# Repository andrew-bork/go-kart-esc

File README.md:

# go-kart-esc
 VROOM, 40A/40A 12-50V Dual Channel Brushed ESC

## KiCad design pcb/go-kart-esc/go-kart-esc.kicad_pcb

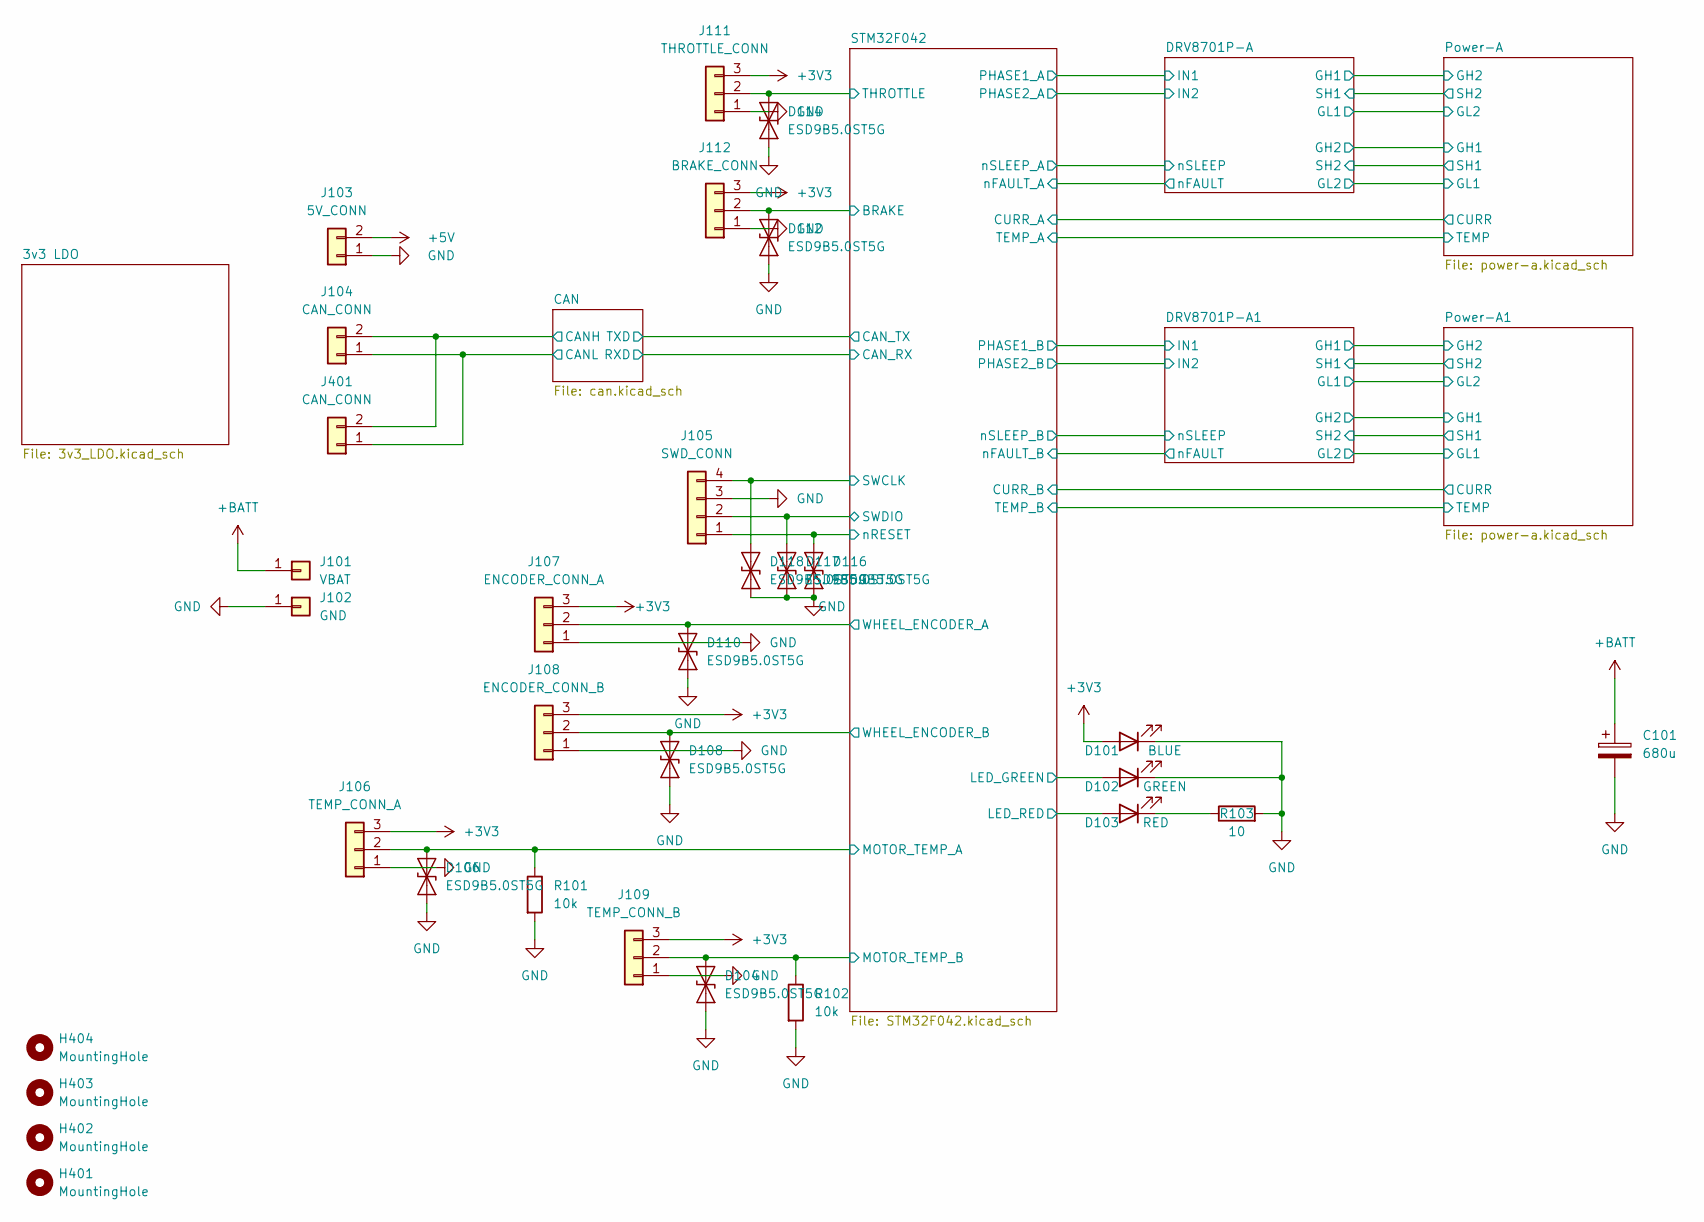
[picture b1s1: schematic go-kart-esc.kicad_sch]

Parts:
C101: 680u; CP_Radial_D16.0mm_P7.50mm
D101: BLUE; LED_0603_1608Metric_Pad1.05x0.95mm_HandSolder
D102: GREEN; LED_0603_1608Metric_Pad1.05x0.95mm_HandSolder
D103: RED; LED_0603_1608Metric_Pad1.05x0.95mm_HandSolder
D104, D106, D108, D110, D112, D114, D116, D117, D118: ESD9B5.0ST5G; D_SOD-923
H401, H402, H403, H404: MountingHole; MountingHole_3.2mm_M3
J101: VBAT; Motor_Solder_Pad
J102: GND; Motor_Solder_Pad
J103: 5V_CONN; JST_XH_S2B-XH-A-1_1x02_P2.50mm_Horizontal
J104, J401: CAN_CONN; JST_XH_S2B-XH-A_1x02_P2.50mm_Horizontal
J105: SWD_CONN; PinHeader_2x02_P2.54mm_Vertical
J106: TEMP_CONN_A; JST_XH_S3B-XH-A_1x03_P2.50mm_Horizontal
J107: ENCODER_CONN_A; JST_XH_S3B-XH-A_1x03_P2.50mm_Horizontal
J108: ENCODER_CONN_B; JST_XH_S3B-XH-A_1x03_P2.50mm_Horizontal
J109: TEMP_CONN_B; JST_XH_S3B-XH-A_1x03_P2.50mm_Horizontal
J111: THROTTLE_CONN; JST_XH_S3B-XH-A_1x03_P2.50mm_Horizontal
J112: BRAKE_CONN; JST_XH_S3B-XH-A_1x03_P2.50mm_Horizontal
R101, R102: 10k; R_0402_1005Metric_Pad0.72x0.64mm_HandSolder
R103: 10; R_0603_1608Metric_Pad0.98x0.95mm_HandSolder

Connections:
+3V3: D101.2 (A), J106.3, J107.3, J108.3, J109.3, J111.3, J112.3; also elsewhere on the board
+5V: J103.2; also elsewhere on the board
+BATT: C101.1, J101.1; also elsewhere on the board
/CAN/CANH: J104.2, J401.2; also elsewhere on the board
/CAN/CANL: J104.1, J401.1; also elsewhere on the board
/STM32F042/BRAKE: D112.2 (A2), J112.2; also elsewhere on the board
/STM32F042/LED_GREEN: D102.2 (A); also elsewhere on the board
/STM32F042/LED_RED: D103.2 (A); also elsewhere on the board
/STM32F042/MOTOR_TEMP_A: D106.2 (A2), J106.2, R101.1; also elsewhere on the board
/STM32F042/MOTOR_TEMP_B: D104.2 (A2), J109.2, R102.1; also elsewhere on the board
/STM32F042/SWCLK: D118.2 (A2), J105.4; also elsewhere on the board
/STM32F042/SWDIO: D117.2 (A2), J105.2; also elsewhere on the board
/STM32F042/THROTTLE: D114.2 (A2), J111.2; also elsewhere on the board
/STM32F042/WHEEL_ENCODER_A: D110.2 (A2), J107.2; also elsewhere on the board
/STM32F042/WHEEL_ENCODER_B: D108.2 (A2), J108.2; also elsewhere on the board
/STM32F042/nRESET: D116.2 (A2), J105.1; also elsewhere on the board
GND: C101.2, D101.1 (K), D102.1 (K), D104.1 (A1), D106.1 (A1), D108.1 (A1), D110.1 (A1), D112.1 (A1), D114.1 (A1), D116.1 (A1), D117.1 (A1), D118.1 (A1), J102.1, J103.1, J105.3, J106.1, J107.1, J108.1, J109.1, J111.1, J112.1, R101.2, R102.2, R103.2; also elsewhere on the board
unnamed: D103.1 (K), R103.1

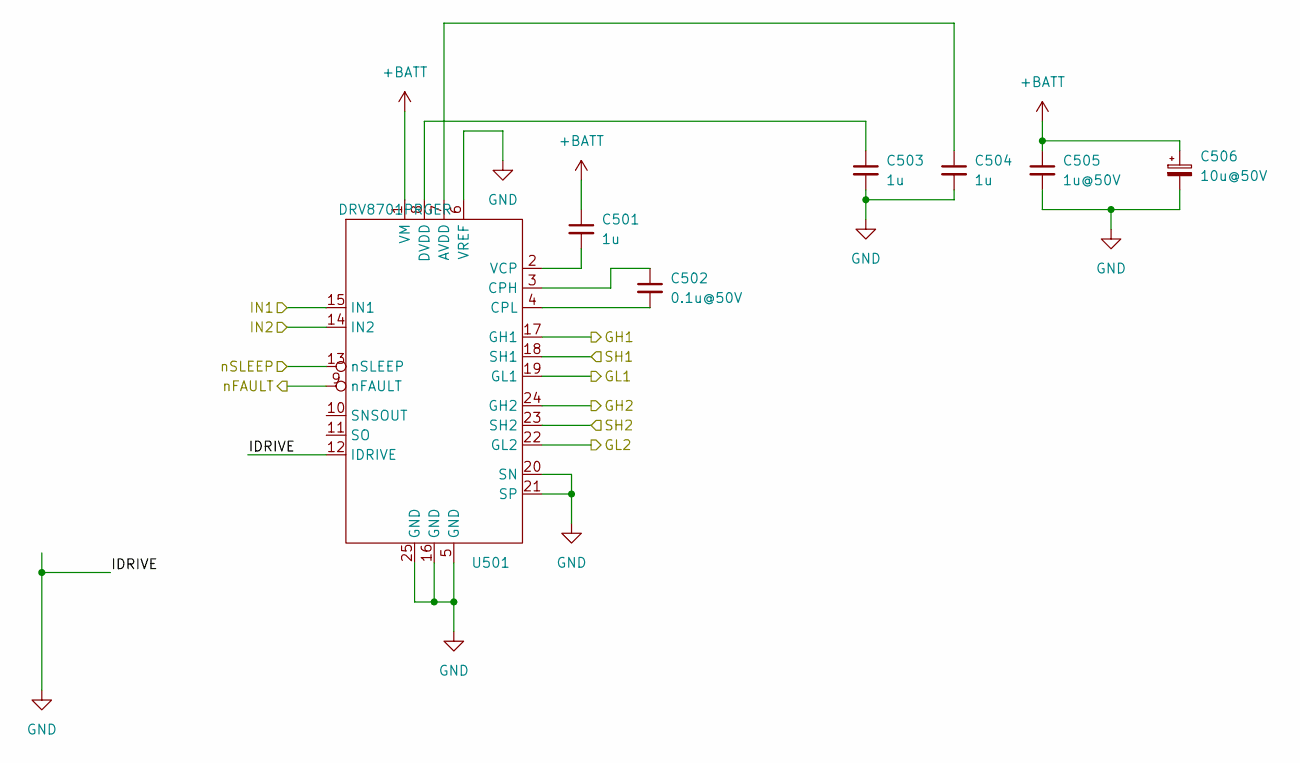
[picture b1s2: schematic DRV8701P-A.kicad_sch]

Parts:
C501, C503, C504: 1u; C_0402_1005Metric_Pad0.74x0.62mm_HandSolder
C502: 0.1u@50V; C_0603_1608Metric_Pad1.08x0.95mm_HandSolder
C505: 1u@50V; C_0402_1005Metric_Pad0.74x0.62mm_HandSolder
C506: 10u@50V; CP_Elec_5x5.8
U501: DRV8701PRGER; Texas_S-PVQFN-N24_EP2.1x2.1mm

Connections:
+BATT: C501.1, C505.1, C506.1, U501.1 (VM); also elsewhere on the board
/DRV8701P-A1/GH1: U501.17 (GH1); also elsewhere on the board
/DRV8701P-A1/GH2: U501.24 (GH2); also elsewhere on the board
/DRV8701P-A1/GL1: U501.19 (GL1); also elsewhere on the board
/DRV8701P-A1/GL2: U501.22 (GL2); also elsewhere on the board
/DRV8701P-A1/IN1: U501.15 (IN1); also elsewhere on the board
/DRV8701P-A1/IN2: U501.14 (IN2); also elsewhere on the board
/DRV8701P-A1/SH1: U501.18 (SH1); also elsewhere on the board
/DRV8701P-A1/SH2: U501.23 (SH2); also elsewhere on the board
/DRV8701P-A1/nFAULT: U501.9 (nFAULT); also elsewhere on the board
/DRV8701P-A1/nSLEEP: U501.13 (nSLEEP); also elsewhere on the board
GND: C503.2, C504.2, C505.2, C506.2, U501.5 (GND), U501.6 (VREF), U501.12 (IDRIVE), U501.16 (GND), U501.20 (SN), U501.21 (SP), U501.25 (GND); also elsewhere on the board
unnamed: C504.1, U501.7 (AVDD)
unnamed: C502.1, U501.3 (CPH)
unnamed: C502.2, U501.4 (CPL)
unnamed: C503.1, U501.8 (DVDD)
unnamed: C501.2, U501.2 (VCP)

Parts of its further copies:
C201, C203, C204: 1u; C_0402_1005Metric_Pad0.74x0.62mm_HandSolder
C202: 0.1u@50V; C_0603_1608Metric_Pad1.08x0.95mm_HandSolder
C205: 1u@50V; C_0402_1005Metric_Pad0.74x0.62mm_HandSolder
C206: 10u@50V; CP_Elec_5x5.8
U201: DRV8701PRGER; Texas_S-PVQFN-N24_EP2.1x2.1mm

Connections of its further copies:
+BATT: C201.1, C205.1, C206.1, U201.1 (VM); also elsewhere on the board
/DRV8701P-A/GH1: U201.17 (GH1); also elsewhere on the board
/DRV8701P-A/GH2: U201.24 (GH2); also elsewhere on the board
/DRV8701P-A/GL1: U201.19 (GL1); also elsewhere on the board
/DRV8701P-A/GL2: U201.22 (GL2); also elsewhere on the board
/DRV8701P-A/IN1: U201.15 (IN1); also elsewhere on the board
/DRV8701P-A/IN2: U201.14 (IN2); also elsewhere on the board
/DRV8701P-A/SH1: U201.18 (SH1); also elsewhere on the board
/DRV8701P-A/SH2: U201.23 (SH2); also elsewhere on the board
/DRV8701P-A/nFAULT: U201.9 (nFAULT); also elsewhere on the board
/DRV8701P-A/nSLEEP: U201.13 (nSLEEP); also elsewhere on the board
GND: C203.2, C204.2, C205.2, C206.2, U201.5 (GND), U201.6 (VREF), U201.12 (IDRIVE), U201.16 (GND), U201.20 (SN), U201.21 (SP), U201.25 (GND); also elsewhere on the board
unnamed: C204.1, U201.7 (AVDD)
unnamed: C202.1, U201.3 (CPH)
unnamed: C202.2, U201.4 (CPL)
unnamed: C203.1, U201.8 (DVDD)
unnamed: C201.2, U201.2 (VCP)

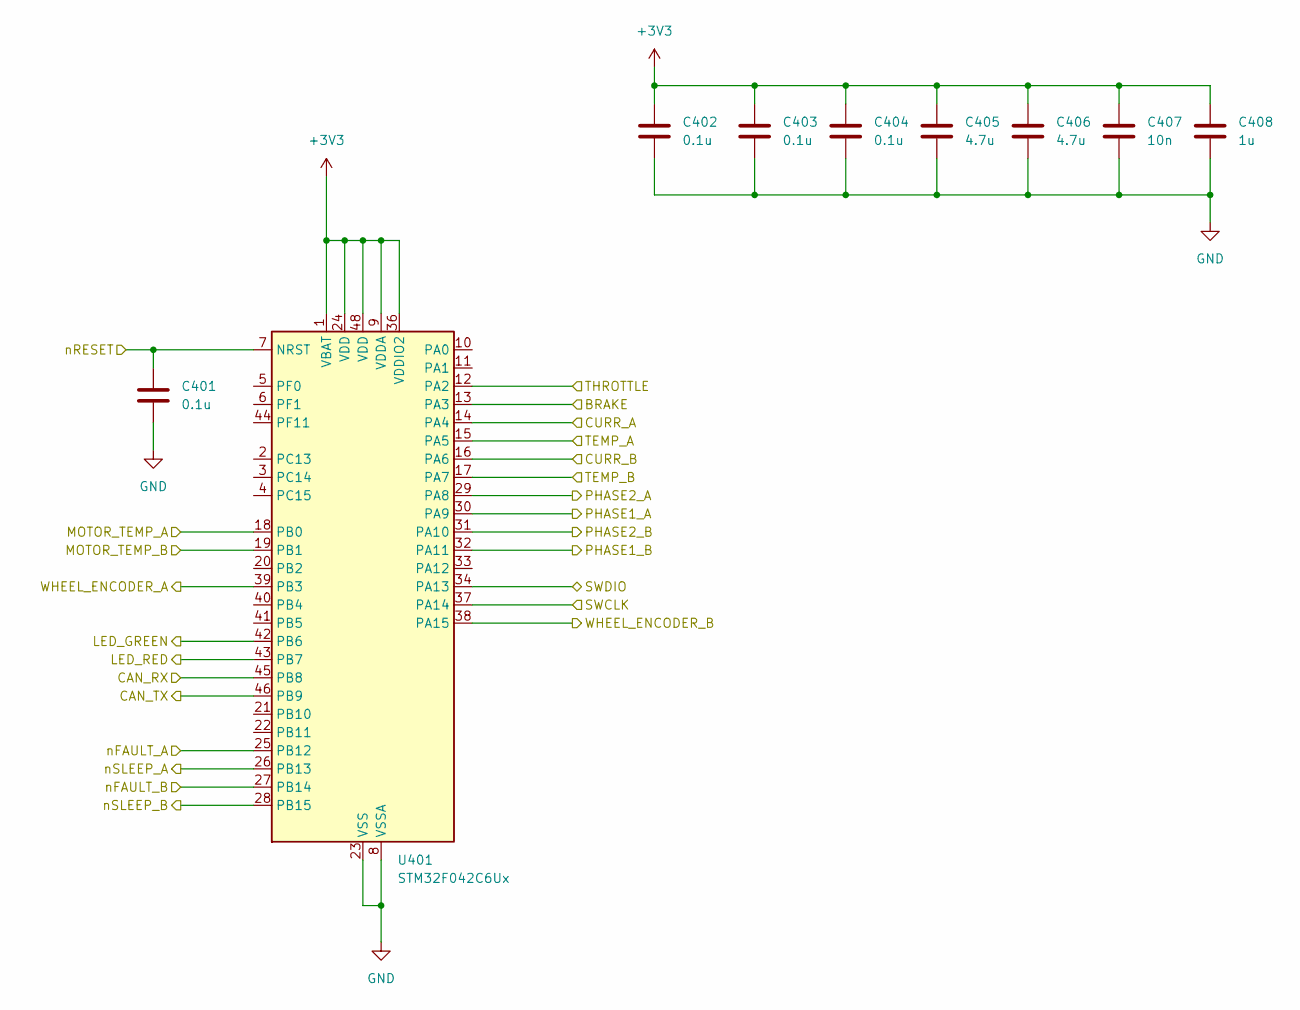
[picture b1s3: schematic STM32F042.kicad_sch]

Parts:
C401, C402, C403, C404: 0.1u; C_0402_1005Metric_Pad0.74x0.62mm_HandSolder
C405, C406: 4.7u; C_0603_1608Metric_Pad1.08x0.95mm_HandSolder
C407: 10n; C_0402_1005Metric_Pad0.74x0.62mm_HandSolder
C408: 1u; C_0402_1005Metric_Pad0.74x0.62mm_HandSolder
U401: STM32F042C6Ux; QFN-48-1EP_7x7mm_P0.5mm_EP5.6x5.6mm

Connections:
+3V3: C402.1, C403.1, C404.1, C405.1, C406.1, C407.1, C408.1, U401.1 (VBAT), U401.9 (VDDA), U401.24 (VDD), U401.36 (VDDIO2), U401.48 (VDD); also elsewhere on the board
/CAN/RXD: U401.45 (PB8); also elsewhere on the board
/CAN/TXD: U401.46 (PB9); also elsewhere on the board
/DRV8701P-A1/IN1: U401.32 (PA11); also elsewhere on the board
/DRV8701P-A1/IN2: U401.31 (PA10); also elsewhere on the board
/DRV8701P-A1/nFAULT: U401.27 (PB14); also elsewhere on the board
/DRV8701P-A1/nSLEEP: U401.28 (PB15); also elsewhere on the board
/DRV8701P-A/IN1: U401.30 (PA9); also elsewhere on the board
/DRV8701P-A/IN2: U401.29 (PA8); also elsewhere on the board
/DRV8701P-A/nFAULT: U401.25 (PB12); also elsewhere on the board
/DRV8701P-A/nSLEEP: U401.26 (PB13); also elsewhere on the board
/Power-A1/CURR: U401.16 (PA6); also elsewhere on the board
/Power-A1/TEMP: U401.17 (PA7); also elsewhere on the board
/Power-A/CURR: U401.14 (PA4); also elsewhere on the board
/Power-A/TEMP: U401.15 (PA5); also elsewhere on the board
/STM32F042/BRAKE: U401.13 (PA3); also elsewhere on the board
/STM32F042/LED_GREEN: U401.42 (PB6); also elsewhere on the board
/STM32F042/LED_RED: U401.43 (PB7); also elsewhere on the board
/STM32F042/MOTOR_TEMP_A: U401.18 (PB0); also elsewhere on the board
/STM32F042/MOTOR_TEMP_B: U401.19 (PB1); also elsewhere on the board
/STM32F042/SWCLK: U401.37 (PA14); also elsewhere on the board
/STM32F042/SWDIO: U401.34 (PA13); also elsewhere on the board
/STM32F042/THROTTLE: U401.12 (PA2); also elsewhere on the board
/STM32F042/WHEEL_ENCODER_A: U401.39 (PB3); also elsewhere on the board
/STM32F042/WHEEL_ENCODER_B: U401.38 (PA15); also elsewhere on the board
/STM32F042/nRESET: C401.1, U401.7 (NRST); also elsewhere on the board
GND: C401.2, C402.2, C403.2, C404.2, C405.2, C406.2, C407.2, C408.2, U401.8 (VSSA), U401.23 (VSS), U401.35 (VSS), U401.47 (VSS), U401.49 (VSS); also elsewhere on the board

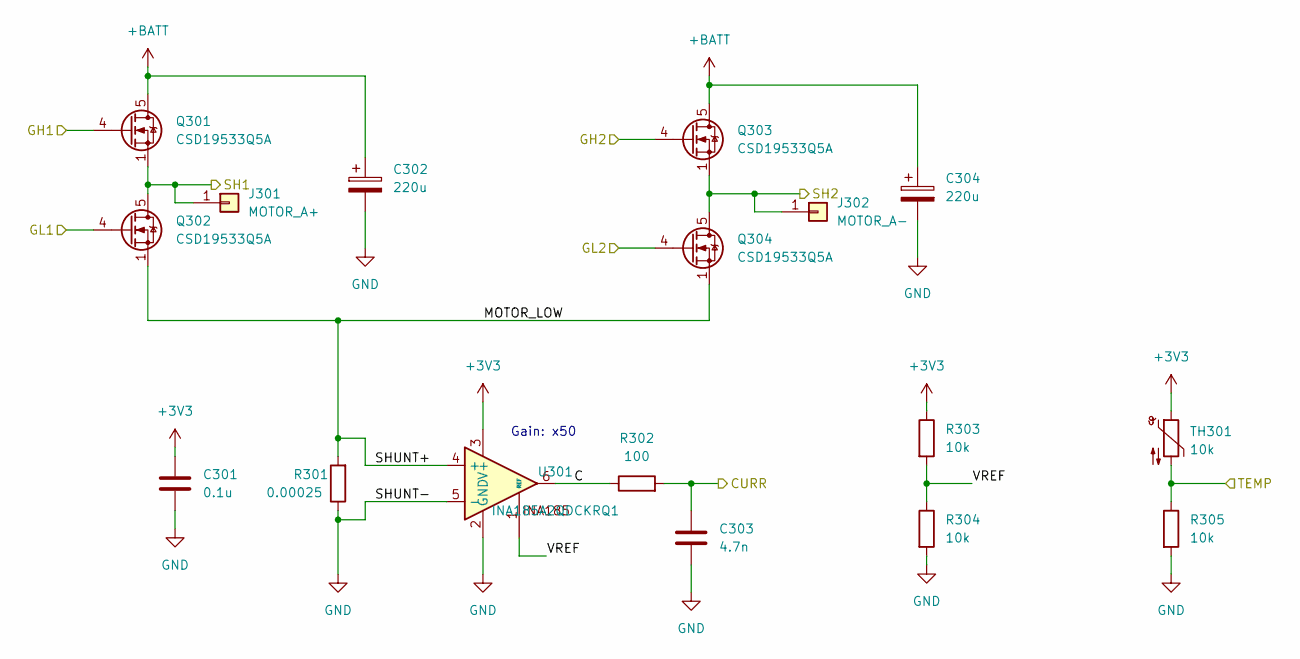
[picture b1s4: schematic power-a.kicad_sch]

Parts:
C301: 0.1u; C_0402_1005Metric_Pad0.74x0.62mm_HandSolder
C302, C304: 220u; CP_Radial_D10.0mm_P5.00mm
C303: 4.7n; C_0603_1608Metric_Pad1.08x0.95mm_HandSolder
J301: MOTOR_A+; Motor_Solder_Pad
J302: MOTOR_A-; Motor_Solder_Pad
Q301, Q302, Q303, Q304: CSD19533Q5A; TDSON-8-1
R301: 0.00025; Shunt_2725
R302: 100; R_0402_1005Metric_Pad0.72x0.64mm_HandSolder
R303, R304, R305: 10k; R_0402_1005Metric_Pad0.72x0.64mm_HandSolder
TH301: 10k; R_0402_1005Metric_Pad0.72x0.64mm_HandSolder
U301: INA185A2QDCKRQ1; SOT-363_SC-70-6_Handsoldering

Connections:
+3V3: C301.1, R303.1, TH301.1, U301.3 (V+); also elsewhere on the board
+BATT: C302.1, C304.1, Q301.5 (D), Q303.5 (D); also elsewhere on the board
/DRV8701P-A/GH1: Q303.4 (G); also elsewhere on the board
/DRV8701P-A/GH2: Q301.4 (G); also elsewhere on the board
/DRV8701P-A/GL1: Q304.4 (G); also elsewhere on the board
/DRV8701P-A/GL2: Q302.4 (G); also elsewhere on the board
/DRV8701P-A/SH1: J302.1, Q303.1 (S), Q303.2 (S), Q303.3 (S), Q304.5 (D); also elsewhere on the board
/DRV8701P-A/SH2: J301.1, Q301.1 (S), Q301.2 (S), Q301.3 (S), Q302.5 (D); also elsewhere on the board
/Power-A/C: R302.1, U301.6
/Power-A/CURR: C303.1, R302.2; also elsewhere on the board
/Power-A/MOTOR_LOW: Q302.1 (S), Q302.2 (S), Q302.3 (S), Q304.1 (S), Q304.2 (S), Q304.3 (S), R301.2, U301.4 (+)
/Power-A/TEMP: R305.1, TH301.2; also elsewhere on the board
/Power-A/VREF: R303.2, R304.1, U301.1 (REF)
GND: C301.2, C302.2, C303.2, C304.2, R301.1, R304.2, R305.2, U301.2 (GND), U301.5 (-); also elsewhere on the board

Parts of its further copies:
C601: 0.1u; C_0402_1005Metric_Pad0.74x0.62mm_HandSolder
C602, C604: 220u; CP_Radial_D10.0mm_P5.00mm
C603: 4.7n; C_0603_1608Metric_Pad1.08x0.95mm_HandSolder
J601: MOTOR_A+; Motor_Solder_Pad
J602: MOTOR_A-; Motor_Solder_Pad
Q601, Q602, Q603, Q604: CSD19533Q5A; TDSON-8-1
R601: 0.00025; Shunt_2725
R602: 100; R_0402_1005Metric_Pad0.72x0.64mm_HandSolder
R603, R604, R605: 10k; R_0402_1005Metric_Pad0.72x0.64mm_HandSolder
TH601: 10k; R_0402_1005Metric_Pad0.72x0.64mm_HandSolder
U601: INA185A2QDCKRQ1; SOT-363_SC-70-6_Handsoldering

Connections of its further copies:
+3V3: C601.1, R603.1, TH601.1, U601.3 (V+); also elsewhere on the board
+BATT: C602.1, C604.1, Q601.5 (D), Q603.5 (D); also elsewhere on the board
/DRV8701P-A1/GH1: Q603.4 (G); also elsewhere on the board
/DRV8701P-A1/GH2: Q601.4 (G); also elsewhere on the board
/DRV8701P-A1/GL1: Q604.4 (G); also elsewhere on the board
/DRV8701P-A1/GL2: Q602.4 (G); also elsewhere on the board
/DRV8701P-A1/SH1: J602.1, Q603.1 (S), Q603.2 (S), Q603.3 (S), Q604.5 (D); also elsewhere on the board
/DRV8701P-A1/SH2: J601.1, Q601.1 (S), Q601.2 (S), Q601.3 (S), Q602.5 (D); also elsewhere on the board
/Power-A1/C: R602.1, U601.6
/Power-A1/CURR: C603.1, R602.2; also elsewhere on the board
/Power-A1/MOTOR_LOW: Q602.1 (S), Q602.2 (S), Q602.3 (S), Q604.1 (S), Q604.2 (S), Q604.3 (S), R601.2, U601.4 (+)
/Power-A1/TEMP: R605.1, TH601.2; also elsewhere on the board
/Power-A1/VREF: R603.2, R604.1, U601.1 (REF)
GND: C601.2, C602.2, C603.2, C604.2, R601.1, R604.2, R605.2, U601.2 (GND), U601.5 (-); also elsewhere on the board

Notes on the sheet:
Gain: x50

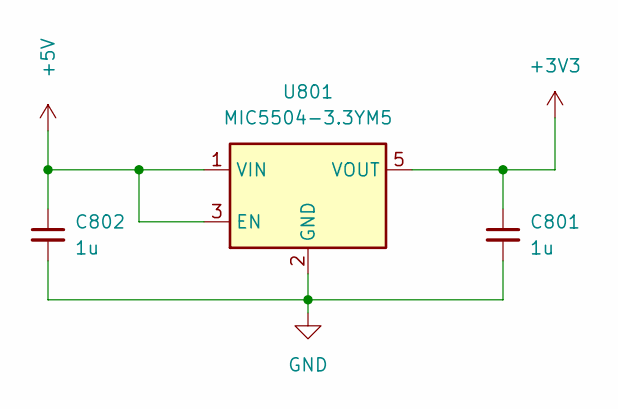
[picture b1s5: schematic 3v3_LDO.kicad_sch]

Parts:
C801, C802: 1u; C_0402_1005Metric_Pad0.74x0.62mm_HandSolder
U801: MIC5504-3.3YM5; SOT-23-5

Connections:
+3V3: C801.1, U801.5 (VOUT); also elsewhere on the board
+5V: C802.1, U801.1 (VIN), U801.3 (EN); also elsewhere on the board
GND: C801.2, C802.2, U801.2 (GND); also elsewhere on the board

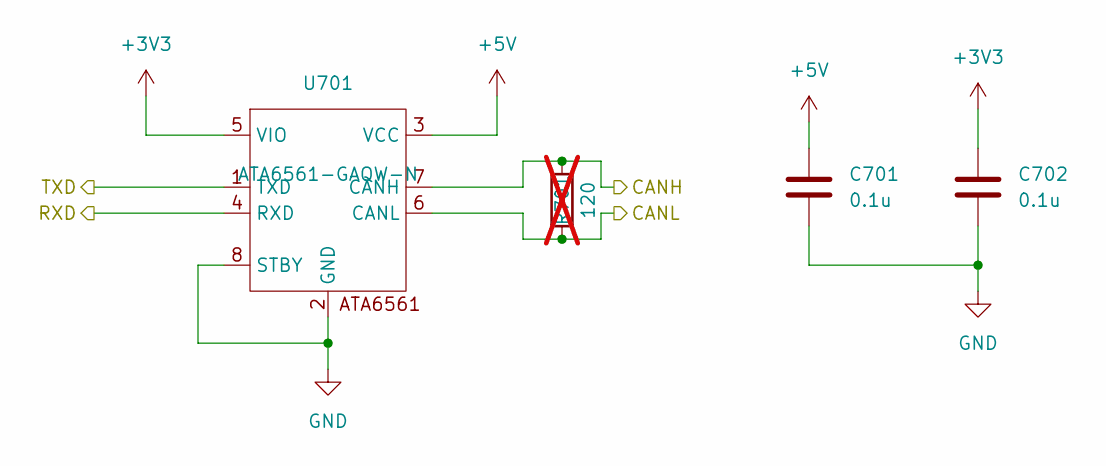
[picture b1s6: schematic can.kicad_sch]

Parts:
C701, C702: 0.1u; C_0402_1005Metric_Pad0.74x0.62mm_HandSolder
R701: 120; R_0402_1005Metric_Pad0.72x0.64mm_HandSolder; not fitted
U701: ATA6561-GAQW-N; SOIC-8-1EP_3.9x4.9mm_P1.27mm_EP2.41x3.3mm

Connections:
+3V3: C702.1, U701.5 (VIO); also elsewhere on the board
+5V: C701.1, U701.3 (VCC); also elsewhere on the board
/CAN/CANH: R701.2, U701.7 (CANH); also elsewhere on the board
/CAN/CANL: R701.1, U701.6 (CANL); also elsewhere on the board
/CAN/RXD: U701.4 (RXD); also elsewhere on the board
/CAN/TXD: U701.1 (TXD); also elsewhere on the board
GND: C701.2, C702.2, U701.2 (GND), U701.8 (STBY); also elsewhere on the board

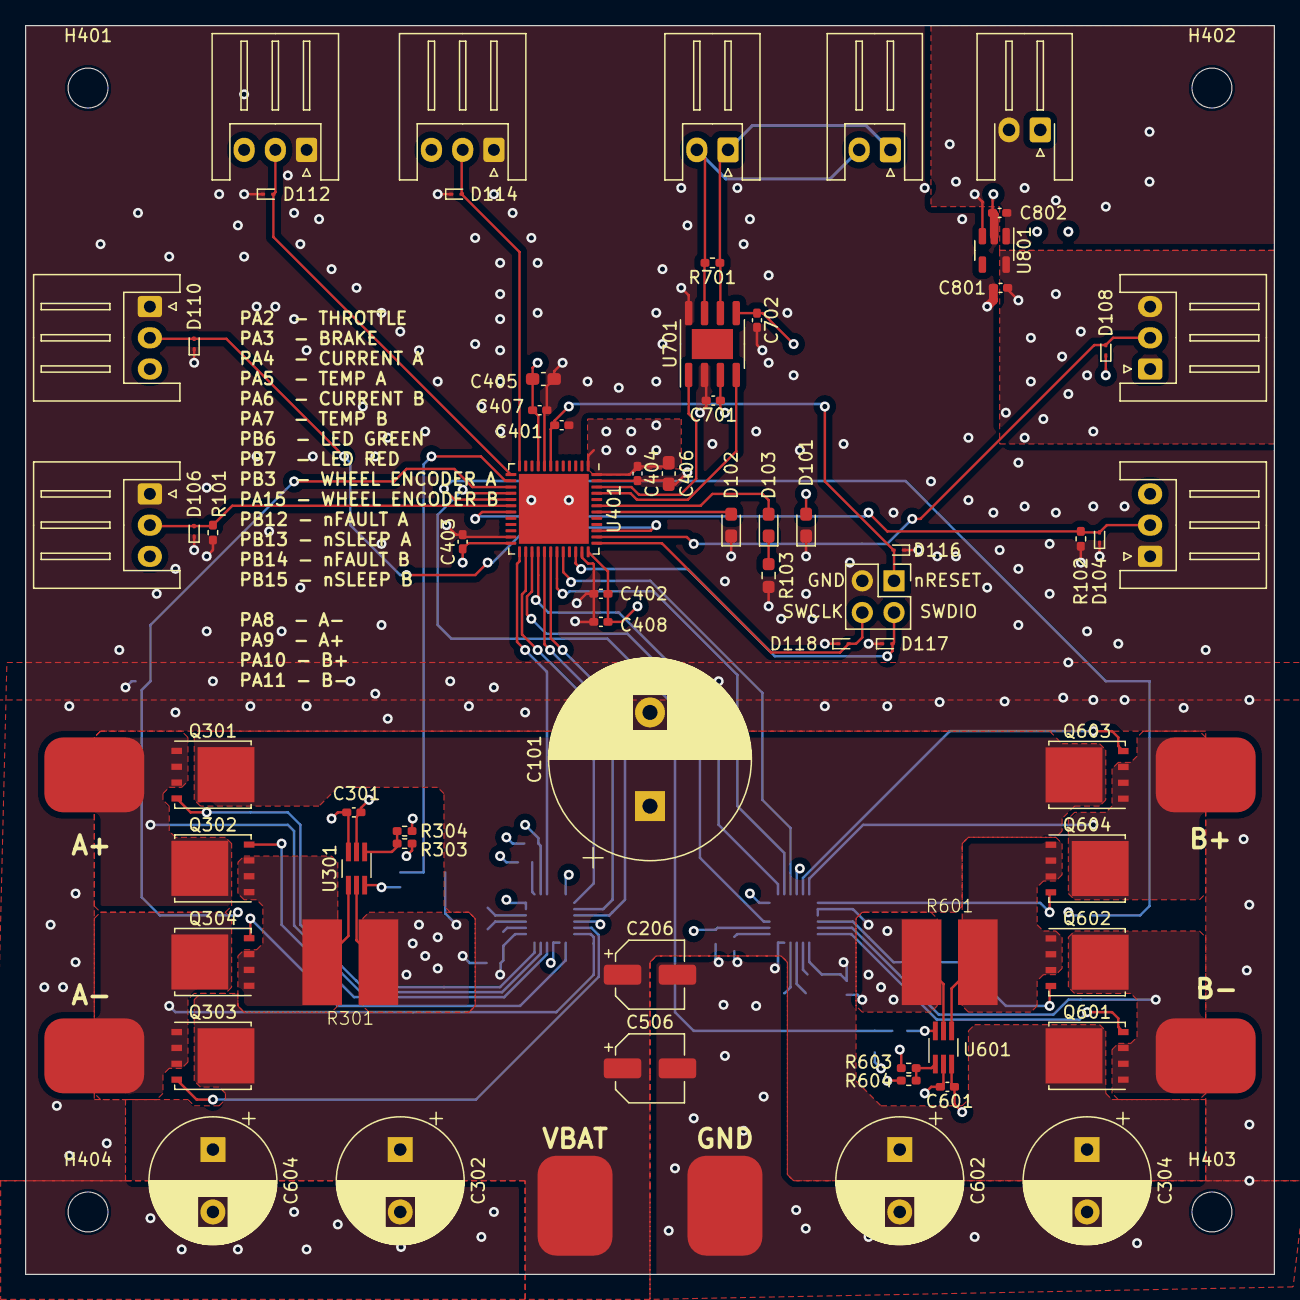
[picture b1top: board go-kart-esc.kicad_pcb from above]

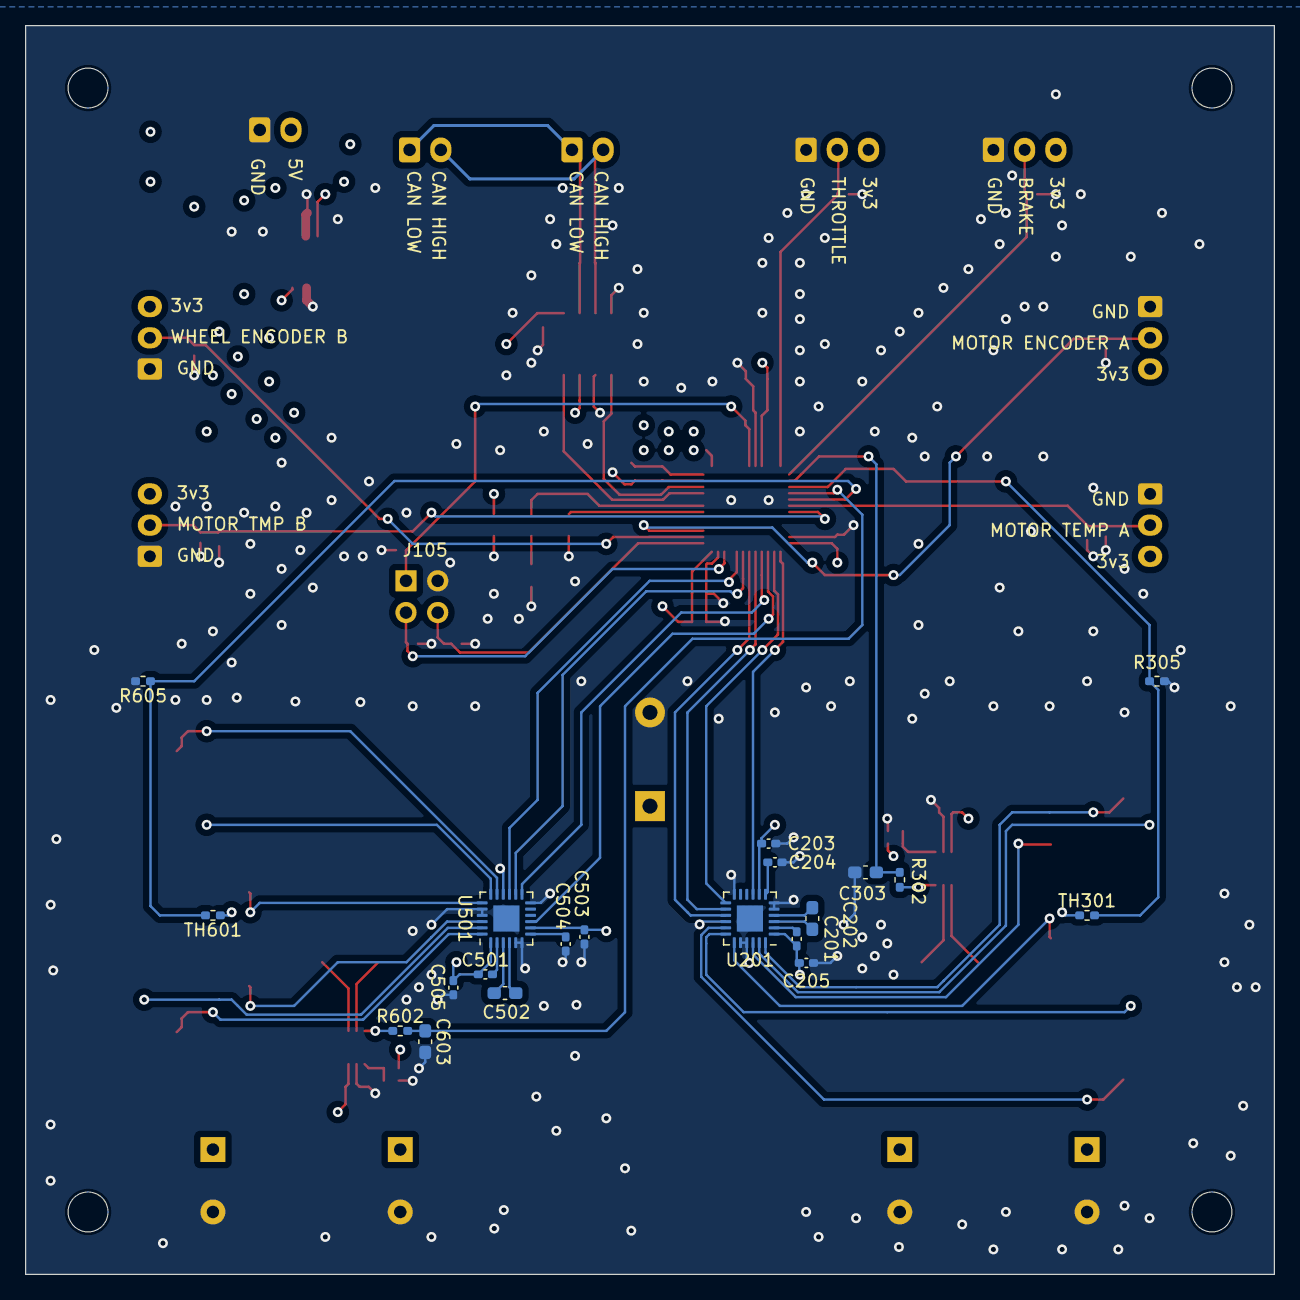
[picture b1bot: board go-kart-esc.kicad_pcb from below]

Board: 4 copper layers, 100.0 x 100.0 mm, 96 parts (20 on the bottom side), 60 nets.

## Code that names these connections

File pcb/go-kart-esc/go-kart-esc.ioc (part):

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Mcu.Name=STM32F042C(4-6)Ux
Mcu.Package=UFQFPN48
Mcu.UserName=STM32F042C6Ux
PA10.Signal=S_TIM1_CH3
PA11.Signal=S_TIM1_CH4
PA13.Mode=Serial_Wire
PA13.Signal=SYS_SWDIO
PA14.Mode=Serial_Wire
PA14.Signal=SYS_SWCLK
PA15.Signal=S_TIM2_CH1_ETR
PA2.Mode=IN2
PA2.Signal=ADC_IN2
PA3.Mode=IN3
PA3.Signal=ADC_IN3
PA4.Mode=IN4
PA4.Signal=ADC_IN4
PA5.Mode=IN5
PA5.Signal=ADC_IN5
PA6.Mode=IN6
PA6.Signal=ADC_IN6
PA7.Mode=IN7
PA7.Signal=ADC_IN7
PA8.Signal=S_TIM1_CH1
PA9.Signal=S_TIM1_CH2
PB0.Mode=IN8
PB0.Signal=ADC_IN8
PB1.Mode=IN9
PB1.Signal=ADC_IN9
PB12.Signal=GPIO_Input
PB13.Signal=GPIO_Output
PB14.Signal=GPIO_Input
PB15.Signal=GPIO_Output
PB3.Signal=S_TIM2_CH2
PB6.Signal=GPIO_Output
PB7.Signal=GPIO_Output
PB8.Mode=CAN_Activate
PB8.Signal=CAN_RX
PB9.Mode=CAN_Activate
PB9.Signal=CAN_TX
board=custom

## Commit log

2024-06-25 Began ESC desgin
2024-06-25 Added resistor shunts
2024-06-27 Poggers
2024-06-28 ooga booga
2024-06-28 updated .gitignore
2024-07-02 Began Routing
2024-07-04 Theory can only take you so far.
2024-07-09 Finished PCB
2024-07-09 Reorganized Directory
